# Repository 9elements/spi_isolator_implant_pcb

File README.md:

The picture shows the spi_implant on the right and the dediprog_interface on the left. The dediprog_interface is connected to the flasher (for example a dediprog). The spi_implant is supposed to be connected to the actual flash chip. The flat cable is connecting both boards. It was originally made to flash laptops and this is why it is composed of two boards (the flat cable can be more easily routed out of the laptop case).

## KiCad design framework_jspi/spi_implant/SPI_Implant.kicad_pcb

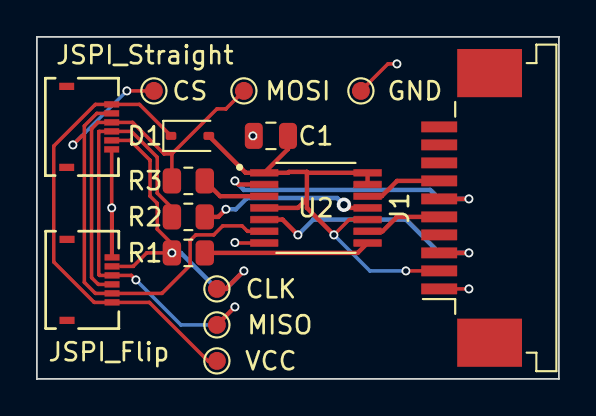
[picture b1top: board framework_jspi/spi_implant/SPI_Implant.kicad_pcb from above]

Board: 2 copper layers, 29.0 x 19.0 mm, 15 parts (0 on the bottom side), 14 nets.

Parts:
C1: 100n; C_0805_2012Metric
CLK: TestPoint_Small; TestPoint_Pad_D1.0mm
CS: TestPoint_Small; TestPoint_Pad_D1.0mm
D1: BAT60A; D_SOD-323
GND: TestPoint_Small; TestPoint_Pad_D1.0mm
J1: Conn_01x10_Socket; TE_1-84952-0_1x10-1MP_P1.0mm_Horizontal
JSPI_Flip: FH19C-6S-0.5SH10; CONN_FH19C-6S-0.5SH10_HIR
JSPI_Straight: FH19C-6S-0.5SH10; CONN_FH19C-6S-0.5SH10_HIR
MISO: TestPoint_Small; TestPoint_Pad_D1.0mm
MOSI: TestPoint_Small; TestPoint_Pad_D1.0mm
R1, R2, R3: 100; R_0805_2012Metric
U2: TMUX1511PWR; SOP65P640X120-14N
VCC: TestPoint_Small; TestPoint_Pad_D1.0mm

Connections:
+3.3V: C1.1, D1.2 (A), J1.2, U2.1 (SEL1), U2.4 (SEL2), U2.10 (SEL3), U2.13 (SEL4), U2.14 (VDD)
CLK: R1.2, U2.8 (D3)
CS1: CS.1 (1_1), JSPI_Flip.5, JSPI_Straight.2, U2.6 (D2)
GND: C1.2, GND.1 (1_1), J1.1, JSPI_Flip.1, JSPI_Straight.6, U2.7 (GND)
MISO: R2.2, U2.11 (D4)
MOSI: R3.2, U2.3 (D1)
unnamed: CLK.1 (1_1), JSPI_Flip.2, JSPI_Straight.5, R1.1
unnamed: D1.1 (K), JSPI_Flip.6, JSPI_Straight.1, VCC.1 (1_1)
unnamed: JSPI_Flip.3, JSPI_Straight.4, MISO.1 (1_1), R2.1
unnamed: JSPI_Flip.4, JSPI_Straight.3, MOSI.1 (1_1), R3.1
P_CLK: J1.5, U2.9 (83)
P_CS1: J1.3, U2.5 (82)
P_MISO: J1.7, U2.12 (S4)
P_MOSI: J1.6, U2.2 (S1)

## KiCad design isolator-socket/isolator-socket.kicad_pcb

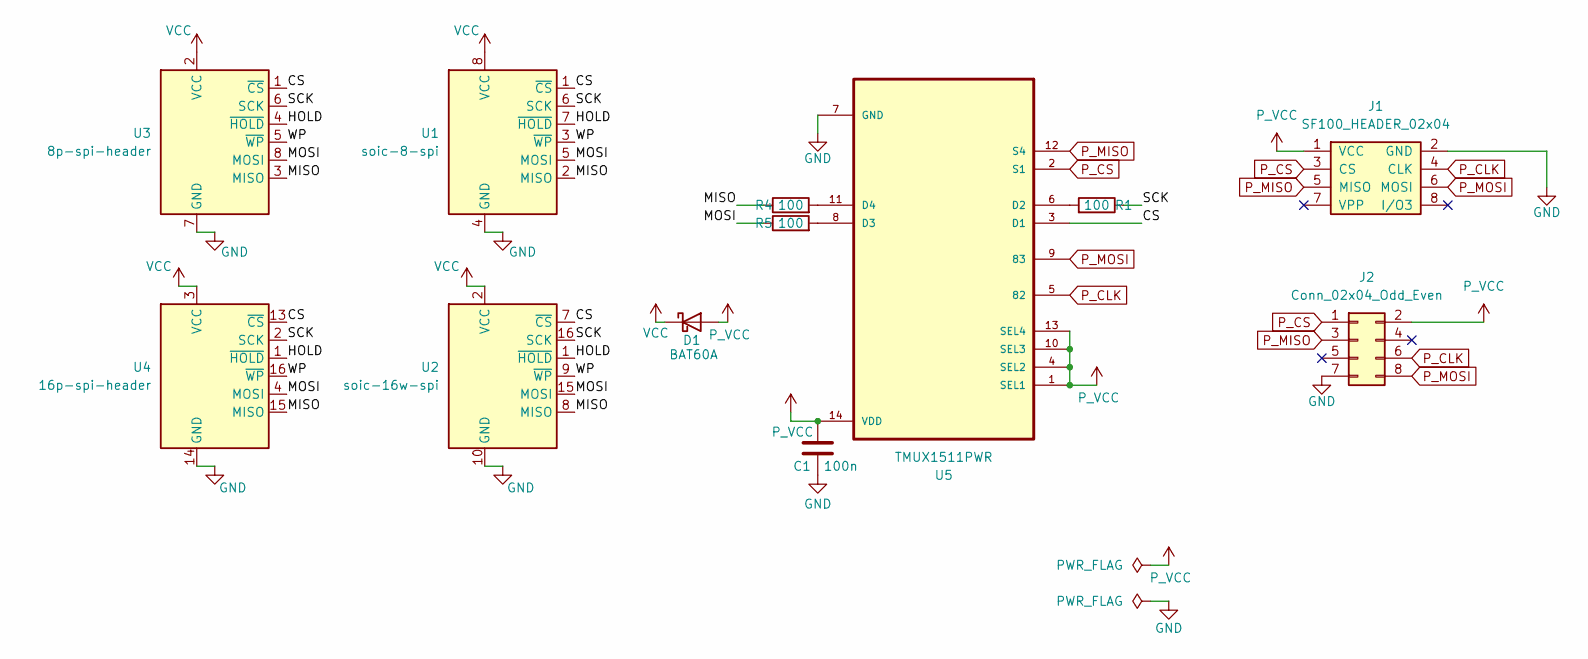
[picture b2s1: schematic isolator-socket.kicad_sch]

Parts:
C1: 100n; C_0805_2012Metric
D1: BAT60A; D_SOD-323
J1: SF100_HEADER_02x04; IDC-Header_2x04_P2.54mm_Vertical_SMD
J2: Conn_02x04_Odd_Even; PinSocket_2x04_P2.54mm_Vertical_SMD
R1, R4, R5: 100; R_0805_2012Metric
U1: soic-8-spi; SOIC-8_3.9x4.9mm_P1.27mm
U2: soic-16w-spi; SOIC-16W_7.5x10.3mm_P1.27mm
U3: 8p-spi-header; PinHeader_2x04_P1.27mm_Vertical_SMD
U4: 16p-spi-header; PinHeader_2x08_P1.27mm_Vertical_SMD
U5: TMUX1511PWR; SOP65P640X120-14N

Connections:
/CS: U1.1 (~CS), U2.7 (~CS), U3.1 (~CS), U4.13 (~CS), U5.3 (D1)
/HOLD: U1.7 (~HOLD), U2.1 (~HOLD), U3.4 (~HOLD), U4.1 (~HOLD)
/MISO: R4.1, U1.2 (MISO), U2.8 (MISO), U3.3 (MISO), U4.15 (MISO)
/MOSI: R5.1, U1.5 (MOSI), U2.15 (MOSI), U3.8 (MOSI), U4.4 (MOSI)
/SCK: R1.1, U1.6 (SCK), U2.16 (SCK), U3.6 (SCK), U4.2 (SCK)
/WP: U1.3 (~WP), U2.9 (~WP), U3.5 (~WP), U4.16 (~WP)
GND: C1.2, J1.2 (GND), J2.7, U1.4 (GND), U2.10 (GND), U3.7 (GND), U4.14 (GND), U5.7 (GND)
unnamed: R1.2, U5.6 (D2)
unnamed: R5.2, U5.8 (D3)
unnamed: R4.2, U5.11 (D4)
P_CLK: J1.4 (CLK), J2.6, U5.5 (82)
P_CS: J1.3 (CS), J2.1, U5.2 (S1)
P_MISO: J1.5 (MISO), J2.3, U5.12 (S4)
P_MOSI: J1.6 (MOSI), J2.8, U5.9 (83)
P_VCC: C1.1, D1.2 (A), J1.1 (VCC), J2.2, U5.1 (SEL1), U5.4 (SEL2), U5.10 (SEL3), U5.13 (SEL4), U5.14 (VDD)
VCC: D1.1 (K), U1.8 (VCC), U2.2 (VCC), U3.2 (VCC), U4.3 (VCC)

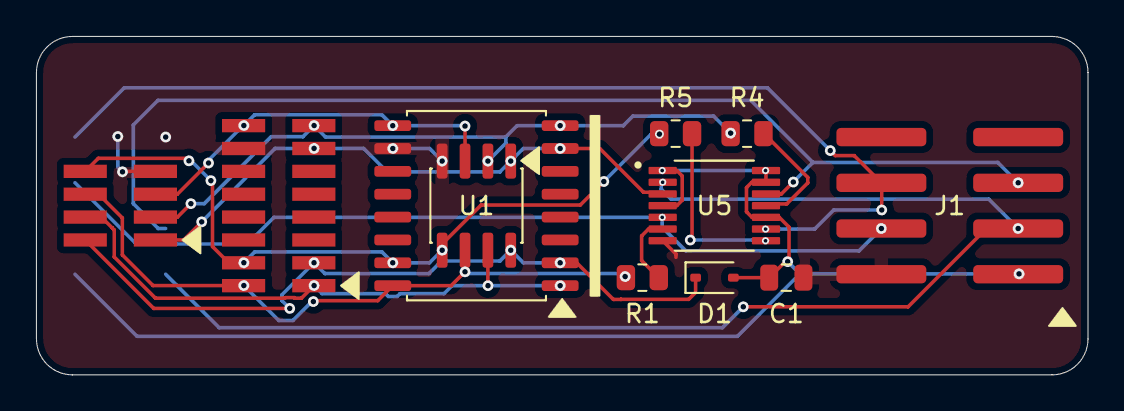
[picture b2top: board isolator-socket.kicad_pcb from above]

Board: 2 copper layers, 58.4 x 18.8 mm, 12 parts (1 on the bottom side), 16 nets.

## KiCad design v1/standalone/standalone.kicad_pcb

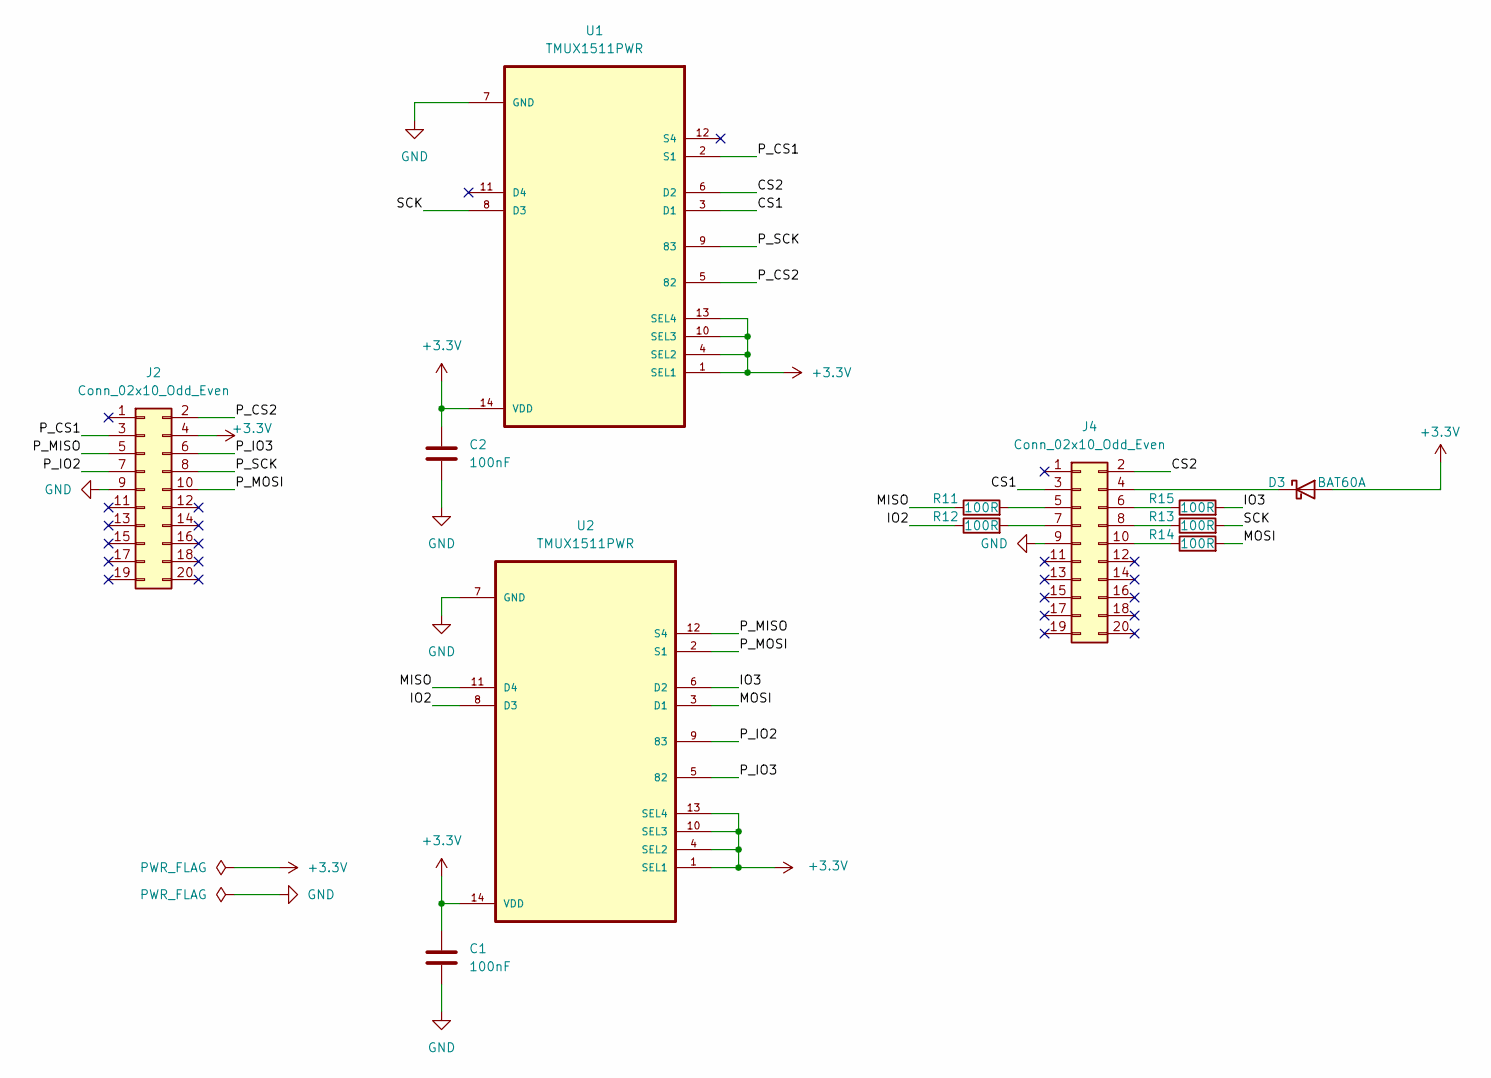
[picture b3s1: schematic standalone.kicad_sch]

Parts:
C1, C2: 100nF; C_0805_2012Metric
D3: BAT60A; D_SOD-323
J2, J4: Conn_02x10_Odd_Even; PinSocket_2x10_P2.54mm_Vertical
R11, R12, R13, R14, R15: 100R; R_0805_2012Metric
U1, U2: TMUX1511PWR; SOP65P640X120-14N

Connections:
+3.3V: C1.1, C2.1, D3.2 (A), J2.4, U1.1 (SEL1), U1.4 (SEL2), U1.10 (SEL3), U1.13 (SEL4), U1.14 (VDD), U2.1 (SEL1), U2.4 (SEL2), U2.10 (SEL3), U2.13 (SEL4), U2.14 (VDD)
/CS1: J4.3, U1.3 (D1)
/CS2: J4.2, U1.6 (D2)
/IO2: R12.1, U2.8 (D3)
/IO3: R15.2, U2.6 (D2)
/MISO: R11.1, U2.11 (D4)
/MOSI: R14.2, U2.3 (D1)
/P_CS1: J2.3, U1.2 (S1)
/P_CS2: J2.2, U1.5 (82)
/P_IO2: J2.7, U2.9 (83)
/P_IO3: J2.6, U2.5 (82)
/P_MISO: J2.5, U2.12 (S4)
/P_MOSI: J2.10, U2.2 (S1)
/P_SCK: J2.8, U1.9 (83)
/SCK: R13.2, U1.8 (D3)
GND: C1.2, C2.2, J2.9, J4.9, U1.7 (GND), U2.7 (GND)
unnamed: D3.1 (K), J4.4
unnamed: J4.5, R11.2
unnamed: J4.6, R15.1
unnamed: J4.7, R12.2
unnamed: J4.8, R13.1
unnamed: J4.10, R14.1

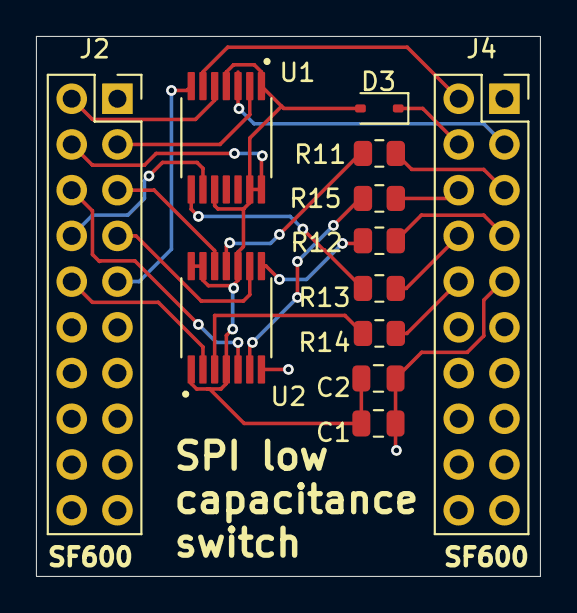
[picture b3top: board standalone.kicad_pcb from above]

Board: 2 copper layers, 28.0 x 30.0 mm, 12 parts (0 on the bottom side), 22 nets.

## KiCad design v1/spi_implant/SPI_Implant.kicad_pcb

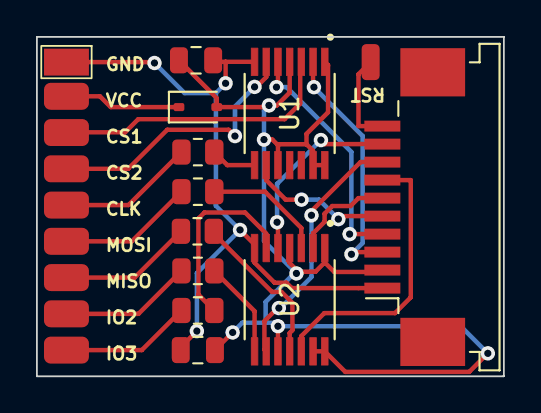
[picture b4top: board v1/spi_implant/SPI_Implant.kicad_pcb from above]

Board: 2 copper layers, 25.9 x 18.9 mm, 13 parts (0 on the bottom side), 23 nets.

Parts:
C1, C2: 100n; C_0805_2012Metric
D1: BAT60A; D_SOD-323
J1: Conn_01x10_Socket; TE_1-84952-0_1x10-1MP_P1.0mm_Horizontal
J2: SPI_Socket; wire_pad_row_1x09-2x3mm
J3: Conn_01x01; SolderWirePad_1x01_SMD_1x2mm
R1, R2, R3, R4, R5: 100; R_0805_2012Metric
U1, U2: TMUX1511PWR; SOP65P640X120-14N

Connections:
+3.3V: C1.1, C2.1, D1.2 (A), J1.2, U1.1 (SEL1), U1.4 (SEL2), U1.10 (SEL3), U1.13 (SEL4), U1.14 (VDD), U2.1 (SEL1), U2.4 (SEL2), U2.10 (SEL3), U2.13 (SEL4), U2.14 (VDD)
CLK: R1.2, U1.8 (D3)
CS1: J2.3, U1.3 (D1)
CS2: J2.4, U1.6 (D2)
GND: C1.2, C2.2, J1.1, J2.1, U1.7 (GND), U2.7 (GND)
IO2: R3.2, U2.8 (D3)
IO3: R2.2, U2.6 (D2)
MISO: R4.2, U2.11 (D4)
MOSI: R5.2, U2.3 (D1)
unnamed: D1.1 (K), J2.2
unnamed: J1.10, J3.1
unnamed: J2.5, R1.1
unnamed: J2.6, R5.1
unnamed: J2.7, R4.1
unnamed: J2.8, R3.1
unnamed: J2.9, R2.1
P_CLK: J1.5, U1.9 (83)
P_CS1: J1.3, U1.2 (S1)
P_CS2: J1.4, U1.5 (82)
P_IO2: J1.8, U2.9 (83)
P_IO3: J1.9, U2.5 (82)
P_MISO: J1.7, U2.12 (S4)
P_MOSI: J1.6, U2.2 (S1)

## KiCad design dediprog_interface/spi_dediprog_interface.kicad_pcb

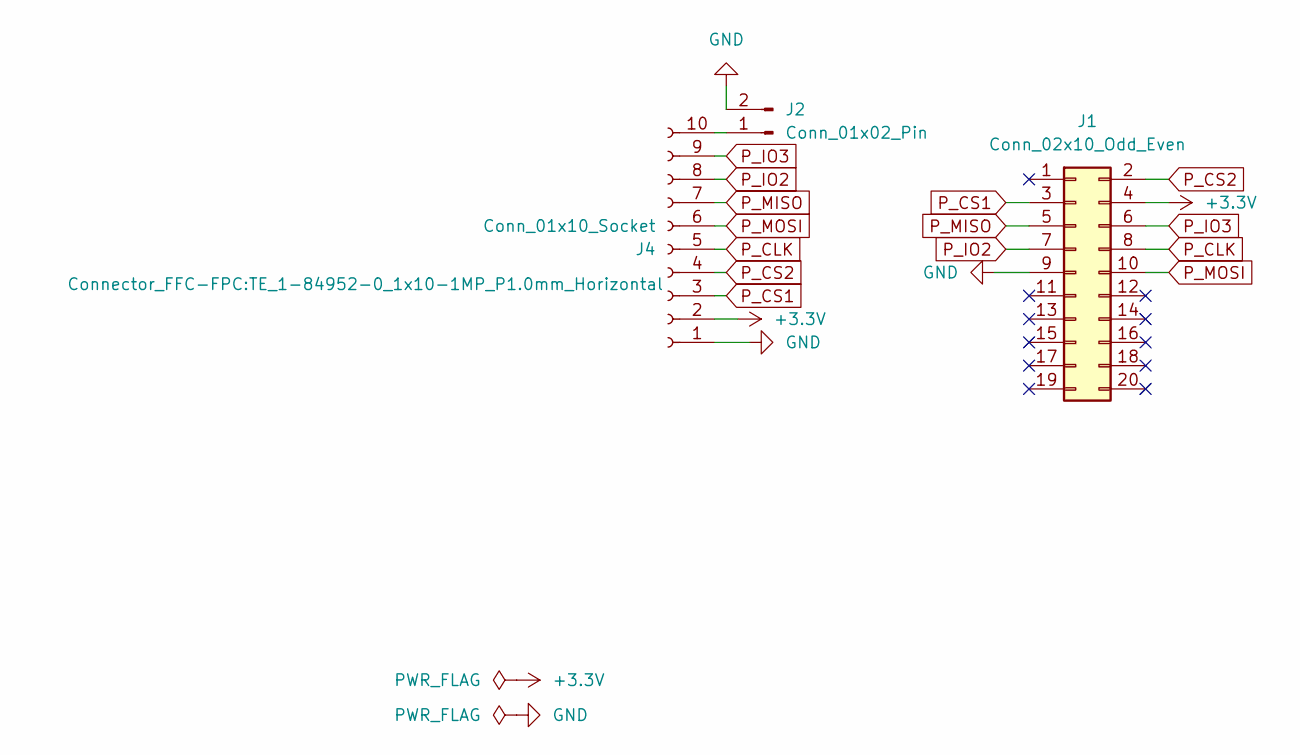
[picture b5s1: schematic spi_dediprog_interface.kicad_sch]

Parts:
J1: Conn_02x10_Odd_Even; PinSocket_2x10_P2.54mm_Vertical
J2: Conn_01x02_Pin; PinHeader_1x02_P2.54mm_Vertical
J4: Conn_01x10_Socket; TE_1-84952-0_1x10-1MP_P1.0mm_Horizontal

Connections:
+3.3V: J1.4, J4.2
GND: J1.9, J2.2, J4.1
unnamed: J2.1, J4.10
P_CLK: J1.8, J4.5
P_CS1: J1.3, J4.3
P_CS2: J1.2, J4.4
P_IO2: J1.7, J4.8
P_IO3: J1.6, J4.9
P_MISO: J1.5, J4.7
P_MOSI: J1.10, J4.6

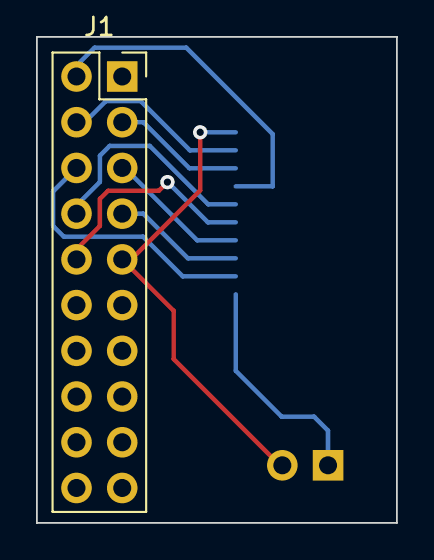
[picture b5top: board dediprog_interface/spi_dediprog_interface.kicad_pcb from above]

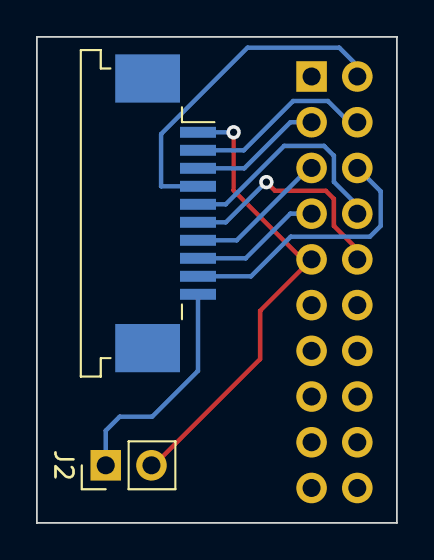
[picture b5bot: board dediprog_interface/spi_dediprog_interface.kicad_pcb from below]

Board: 2 copper layers, 20.0 x 27.0 mm, 3 parts (2 on the bottom side), 10 nets.

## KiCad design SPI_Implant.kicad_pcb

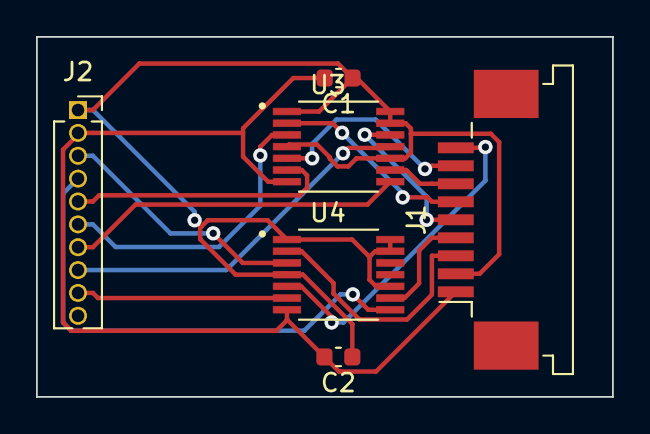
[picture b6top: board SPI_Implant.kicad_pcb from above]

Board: 2 copper layers, 32.0 x 20.0 mm, 6 parts (0 on the bottom side), 16 nets.

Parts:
C1, C2: 100n; C_0603_1608Metric
J1: Dediprog_FPC; TE_84952-9_1x09-1MP_P1.0mm_Horizontal
J2: SPI_Socket; PinSocket_1x10_P1.27mm_Vertical
U3, U4: TMUX1511PWR; SOP65P640X120-14N

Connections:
+3.3V: C1.1, C2.1, J1.2, J2.1, U3.1 (SEL1), U3.4 (SEL2), U3.10 (SEL3), U3.13 (SEL4), U3.14 (VDD), U4.1 (SEL1), U4.4 (SEL2), U4.10 (SEL3), U4.13 (SEL4), U4.14 (VDD)
CLK: J2.4, U4.8 (D3)
CS1: J2.3, U4.3 (D1)
CS2: J2.9, U4.6 (D2)
GND: C1.2, C2.2, J1.1, J2.2, U3.7 (GND), U4.7 (GND)
IO2: J2.7, U3.8 (D3)
IO3: J2.8, U3.11 (D4)
MISO: J2.5, U3.6 (D2)
MOSI: J2.6, U3.3 (D1)
P_CLK: J1.4, U4.9 (83)
P_CS1: J1.3, U4.2 (S1)
P_CS2: J1.9, U4.5 (82)
P_IO2: J1.7, U3.9 (83)
P_IO3: J1.8, U3.5 (82)
P_MISO: J1.5, U3.12 (S4)
P_MOSI: J1.6, U3.2 (S1)

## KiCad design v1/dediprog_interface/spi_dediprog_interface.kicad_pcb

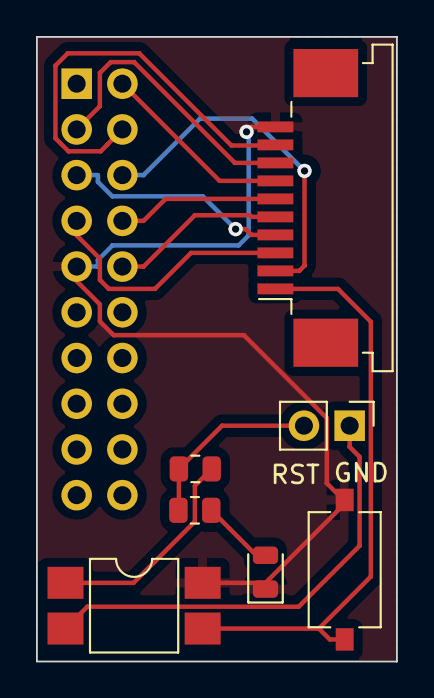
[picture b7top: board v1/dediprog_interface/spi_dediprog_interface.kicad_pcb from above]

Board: 2 copper layers, 20.0 x 34.7 mm, 8 parts (1 on the bottom side), 14 nets.

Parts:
D1: LED; LED_0805_2012Metric
J1: Conn_02x10_Odd_Even; PinSocket_2x10_P2.54mm_Vertical
J3: Conn_01x02_Pin; PinHeader_1x02_P2.54mm_Vertical
J4: Conn_01x10_Socket; TE_1-84952-0_1x10-1MP_P1.0mm_Horizontal
R1: R100; R_0805_2012Metric
R2: R300; R_0805_2012Metric
SW1: SW_Push; SW_Tactile_SPST_NO_Straight_CK_PTS636Sx25SMTRLFS
U1: SMDIP-4_W7.62mm

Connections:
+3.3V: J1.4, J4.9
GND: D1.1 (K), J1.9, J4.10, SW1.1, U1.4
unnamed: D1.2 (A), R2.1
unnamed: J3.1, U1.2
unnamed: J3.2, R1.1, R2.2
unnamed: J4.1, SW1.2, U1.3
unnamed: R1.2, U1.1
P_CLK: J1.8, J4.6
P_CS1: J1.3, J4.8
P_CS2: J1.2, J4.7
P_IO2: J1.7, J4.3
P_IO3: J1.6, J4.2
P_MISO: J1.5, J4.4
P_MOSI: J1.10, J4.5

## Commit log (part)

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2024-03-12 Fixed ERC errors
2024-03-12 updated footprints and routing, added labels
2024-03-12 Add dediprog interface
2024-03-12 change to versioned directories
2024-08-05 WIP: Redesign
2024-11-05 Add README.md
2025-03-27 Add standalone version
